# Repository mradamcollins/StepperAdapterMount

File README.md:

# StepperAdapterMount
Adapter plates for mounting super tiny stepper motors

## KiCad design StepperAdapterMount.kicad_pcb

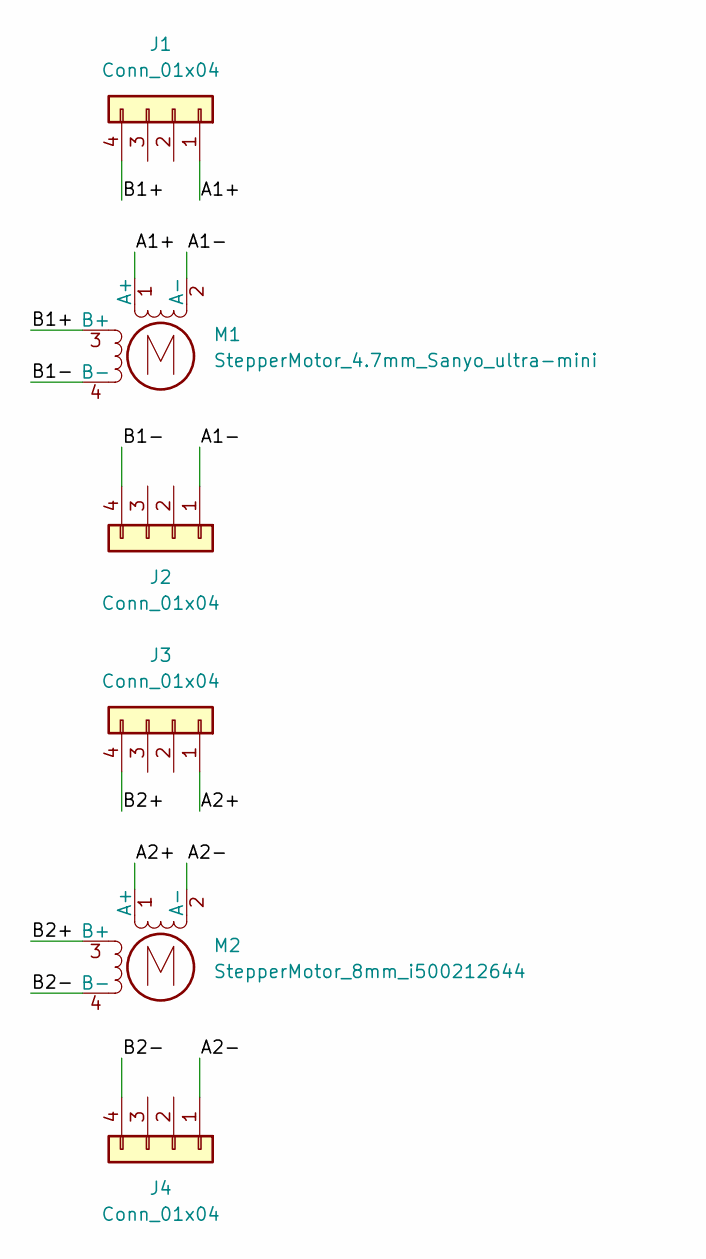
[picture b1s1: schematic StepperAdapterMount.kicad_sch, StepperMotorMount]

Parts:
J1, J2, J3, J4: Conn_01x04; PinHeader_1x04_P2.54mm_Vertical
M1: StepperMotor_4.7mm_Sanyo_ultra-mini
M2: StepperMotor_8mm_i500212644

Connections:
/A1+: J1.1, M1.1 (A+)
/A1-: J2.1, M1.2 (A-)
/A2+: J3.1, M2.1 (A+)
/A2-: J4.1, M2.2 (A-)
/B1+: J1.4, M1.3 (B+)
/B1-: J2.4, M1.4 (B-)
/B2+: J3.4, M2.3 (B+)
/B2-: J4.4, M2.4 (B-)

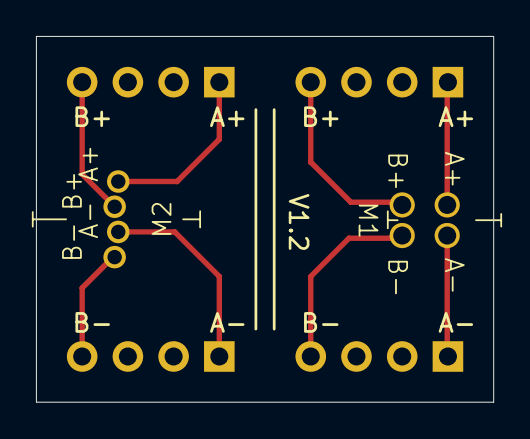
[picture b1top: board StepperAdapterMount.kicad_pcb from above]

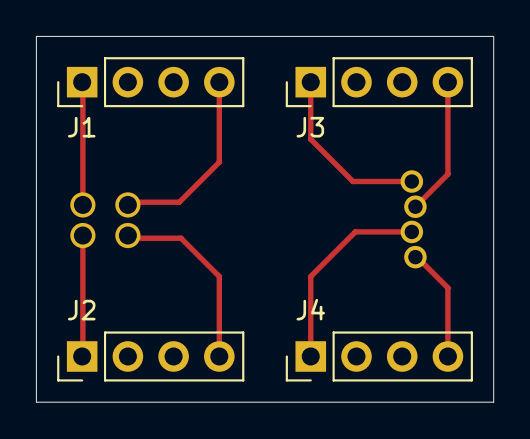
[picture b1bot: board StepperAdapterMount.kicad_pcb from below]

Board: 2 copper layers, 25.4 x 20.3 mm, 6 parts (4 on the bottom side), 8 nets.

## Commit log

2024-11-26 adding gitignore
2024-12-04 Update 3d models in library
2024-12-04 Updated board shape
2024-12-16 v1.0
2024-12-16 changed library for smaller hole size
2025-01-06 updated hole spacing for v1.2
